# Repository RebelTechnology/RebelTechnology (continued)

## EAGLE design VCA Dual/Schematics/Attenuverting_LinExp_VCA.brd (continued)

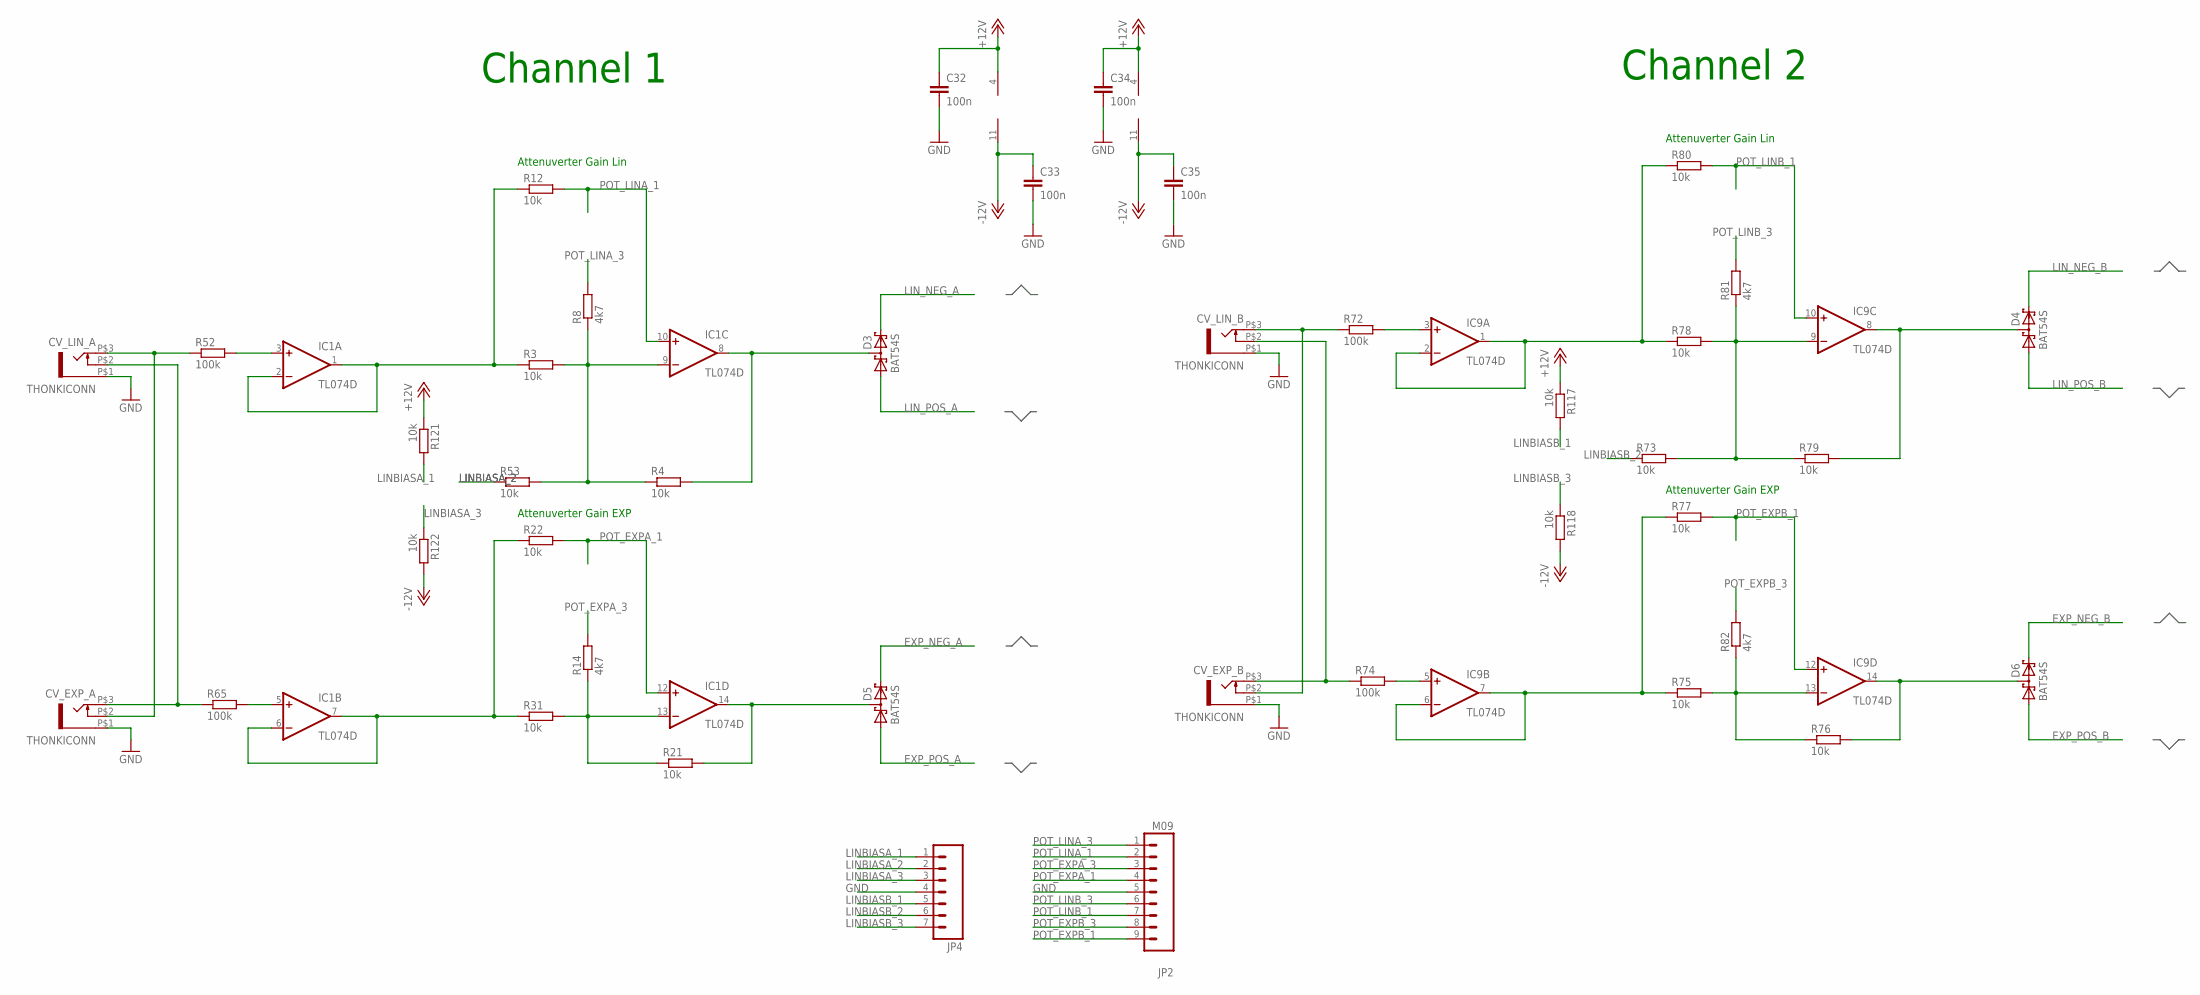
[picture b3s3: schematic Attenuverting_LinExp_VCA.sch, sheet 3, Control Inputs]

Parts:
C32, C33, C34, C35: 100n; C0603K
CV_EXP_A: THONKICONN
CV_EXP_B: THONKICONN
CV_LIN_A: THONKICONN
CV_LIN_B: THONKICONN
D3, D4, D5, D6: BAT54S; SOT23
IC1, IC9: TL074D; SO14
JP2: M09; 1X09
JP4: M07; 1X07
R3, R4, R12, R21, R22, R31, R53, R73, R75, R76, R77, R78, R79, R80, R117, R118, R121, R122: 10k; 0603
R8, R14, R81, R82: 4k7; 0603
R52, R65, R72, R74: 100k; 0603

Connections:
+12V: C32.1, C34.1, IC1.4 (V+), IC9.4 (V+), R117.1, R121.1; also elsewhere on the board
-12V: C33.1, C35.1, IC1.11 (V-), IC9.11 (V-), R118.2, R122.2; also elsewhere on the board
CV_1+: IC1.6 (-IN), IC1.7 (OUT), R22.1, R31.1
CV_1+1: IC9.6 (-IN), IC9.7 (OUT), R75.1, R77.1
CV_1-: IC1.1 (OUT), IC1.2 (-IN), R3.1, R12.1
CV_1-1: IC9.1 (OUT), IC9.2 (-IN), R78.1, R80.1
EXP_NEG_A: D5.2 (C2); also elsewhere on the board
EXP_NEG_B: D6.2 (C2); also elsewhere on the board
EXP_POS_A: D5.1 (A1); also elsewhere on the board
EXP_POS_B: D6.1 (A1); also elsewhere on the board
GND: C32.2, C33.2, C34.2, C35.2, CV_EXP_A.P$1 (5), CV_EXP_B.P$1 (5), CV_LIN_A.P$1 (5), CV_LIN_B.P$1 (5), JP2.5, JP4.4; also elsewhere on the board
LINBIASA_1: JP4.1, R121.2; also elsewhere on the board
LINBIASA_2: JP4.2, R53.1; also elsewhere on the board
LINBIASA_3: JP4.3, R122.1; also elsewhere on the board
LINBIASB_1: JP4.5, R117.2; also elsewhere on the board
LINBIASB_2: JP4.6, R73.1; also elsewhere on the board
LINBIASB_3: JP4.7, R118.1; also elsewhere on the board
LIN_NEG_A: D3.2 (C2); also elsewhere on the board
LIN_NEG_B: D4.2 (C2); also elsewhere on the board
LIN_POS_A: D3.1 (A1); also elsewhere on the board
LIN_POS_B: D4.1 (A1); also elsewhere on the board
unnamed: D3.3 (C1A2), IC1.8 (OUT), R4.2
unnamed: IC1.3 (+IN), R52.2
unnamed: IC1.5 (+IN), R65.2
unnamed: IC1.13 (-IN), R14.1, R21.1, R31.2
unnamed: IC1.9 (-IN), R3.2, R4.1, R8.1, R53.2
unnamed: CV_EXP_B.P$3 (3), CV_LIN_B.P$2 (4), R74.1
unnamed: CV_EXP_B.P$2 (4), CV_LIN_B.P$3 (3), R72.1
unnamed: D6.3 (C1A2), IC9.14 (OUT), R76.2
unnamed: IC9.13 (-IN), R75.2, R76.1, R82.1
unnamed: D4.3 (C1A2), IC9.8 (OUT), R79.2
unnamed: IC9.3 (+IN), R72.2
unnamed: IC9.5 (+IN), R74.2
unnamed: IC9.9 (-IN), R73.2, R78.2, R79.1, R81.1
unnamed: CV_EXP_A.P$3 (3), CV_LIN_A.P$2 (4), R65.1
unnamed: CV_EXP_A.P$2 (4), CV_LIN_A.P$3 (3), R52.1
unnamed: D5.3 (C1A2), IC1.14 (OUT), R21.2
POT_EXPA_1: IC1.12 (+IN), JP2.4, R22.2; also elsewhere on the board
POT_EXPA_3: JP2.3, R14.2; also elsewhere on the board
POT_EXPB_1: IC9.12 (+IN), JP2.9, R77.2; also elsewhere on the board
POT_EXPB_3: JP2.8, R82.2; also elsewhere on the board
POT_LINA_1: IC1.10 (+IN), JP2.2, R12.2; also elsewhere on the board
POT_LINA_3: JP2.1, R8.2; also elsewhere on the board
POT_LINB_1: IC9.10 (+IN), JP2.7, R80.2; also elsewhere on the board
POT_LINB_3: JP2.6, R81.2; also elsewhere on the board

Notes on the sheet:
Attenuverter Gain Lin
Attenuverter Gain EXP
Channel 1
Channel 2

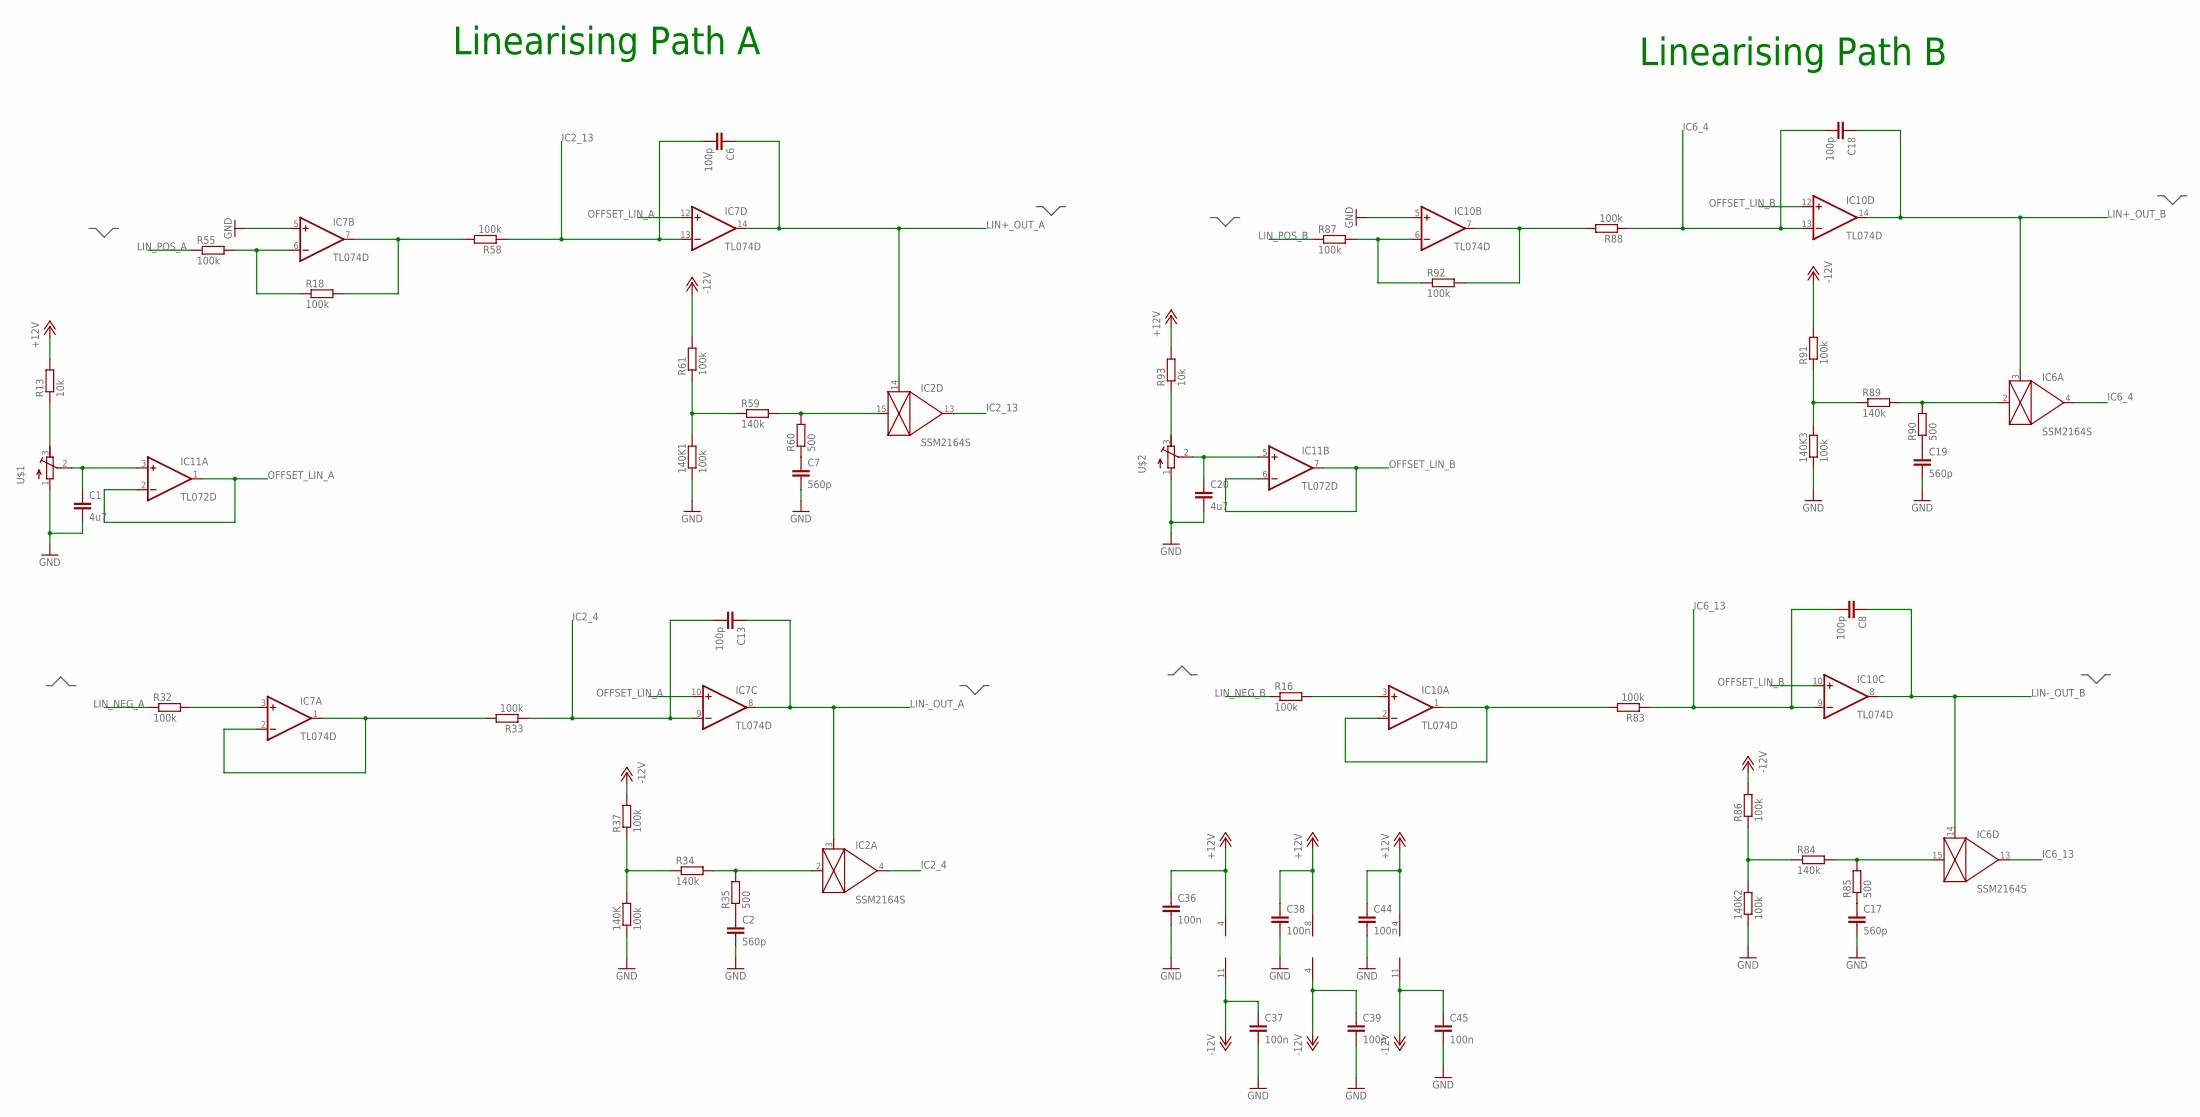
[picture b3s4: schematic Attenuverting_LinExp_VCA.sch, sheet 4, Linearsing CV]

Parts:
140K, 140K1, 140K2, 140K3: 100k; 0603
C1, C20: 4u7; C0603K
C2, C7, C17, C19: 560p; C0603K
C6, C8, C13, C18: 100p; C0603K
C36, C37, C38, C39, C44, C45: 100n; C0603K
IC2, IC6: SSM2164S; SOIC16N
IC7, IC10: TL074D; SO14
IC11: TL072D; SO08
R13, R93: 10k; 0603
R16, R18, R32, R33, R37, R55, R58, R61, R83, R86, R87, R88, R91, R92: 100k; 0603
R34, R59, R84, R89: 140k; 0603
R35, R60, R85, R90: 500; 0603
U$1, U$2: R-TRIMM64W; RTRIM64W

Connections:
+12V: C36.1, C38.1, C44.1, IC7.4 (V+), IC10.4 (V+), IC11.8 (V+), R13.2, R93.2; also elsewhere on the board
-10V: 140K.2, R34.1, R37.1
-10V1: 140K1.2, R59.1, R61.1
-10V2: 140K3.2, R89.1, R91.1
-10V3: 140K2.2, R84.1, R86.1
-12V: C37.1, C39.1, C45.1, IC7.11 (V-), IC10.11 (V-), IC11.4 (V-), R37.2, R61.2, R86.2, R91.2; also elsewhere on the board
GND: 140K.1, 140K1.1, 140K2.1, 140K3.1, C1.2, C2.2, C7.2, C17.2, C19.2, C20.2, C36.2, C37.2, C38.2, C39.2, C44.2, C45.2, IC7.5 (+IN), IC10.5 (+IN), U$1.1 (A), U$2.1 (A); also elsewhere on the board
IC2_4: C13.2, IC2.4 (OUT), IC7.9 (-IN), R33.1
IC2_13: C6.2, IC2.13 (OUT), IC7.13 (-IN), R58.1
IC6_4: C18.2, IC6.4 (OUT), IC10.13 (-IN), R88.1
IC6_13: C8.2, IC6.13 (OUT), IC10.9 (-IN), R83.1
LIN+_OUT_A: C6.1, IC2.14 (CTRL), IC7.14 (OUT); also elsewhere on the board
LIN+_OUT_B: C18.1, IC6.3 (CTRL), IC10.14 (OUT); also elsewhere on the board
LIN-_OUT_A: C13.1, IC2.3 (CTRL), IC7.8 (OUT); also elsewhere on the board
LIN-_OUT_B: C8.1, IC6.14 (CTRL), IC10.8 (OUT); also elsewhere on the board
LIN_NEG_A: R32.1; also elsewhere on the board
LIN_NEG_B: R16.1; also elsewhere on the board
LIN_POS_A: R55.1; also elsewhere on the board
LIN_POS_B: R87.1; also elsewhere on the board
unnamed: IC7.1 (OUT), IC7.2 (-IN), R33.2
unnamed: C2.1, R35.1
unnamed: IC2.2 (IN), R34.2, R35.2
unnamed: IC7.6 (-IN), R18.1, R55.2
unnamed: IC10.7 (OUT), R88.2, R92.2
unnamed: C19.1, R90.1
unnamed: R13.1, U$1.3 (E)
unnamed: C1.1, IC11.3 (+IN), U$1.2 (S)
unnamed: IC7.3 (+IN), R32.2
unnamed: IC7.7 (OUT), R18.2, R58.2
unnamed: C7.1, R60.1
unnamed: IC2.15 (IN), R59.2, R60.2
unnamed: IC6.2 (IN), R89.2, R90.2
unnamed: IC10.1 (OUT), IC10.2 (-IN), R83.2
unnamed: IC10.3 (+IN), R16.2
unnamed: C17.1, R85.1
unnamed: IC6.15 (IN), R84.2, R85.2
unnamed: IC10.6 (-IN), R87.2, R92.1
unnamed: R93.1, U$2.3 (E)
unnamed: C20.1, IC11.5 (+IN), U$2.2 (S)
OFFSET_LIN_A: IC7.10 (+IN), IC7.12 (+IN), IC11.1 (OUT), IC11.2 (-IN)
OFFSET_LIN_B: IC10.10 (+IN), IC10.12 (+IN), IC11.6 (-IN), IC11.7 (OUT)

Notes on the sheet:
Linearising Path A
Linearising Path B

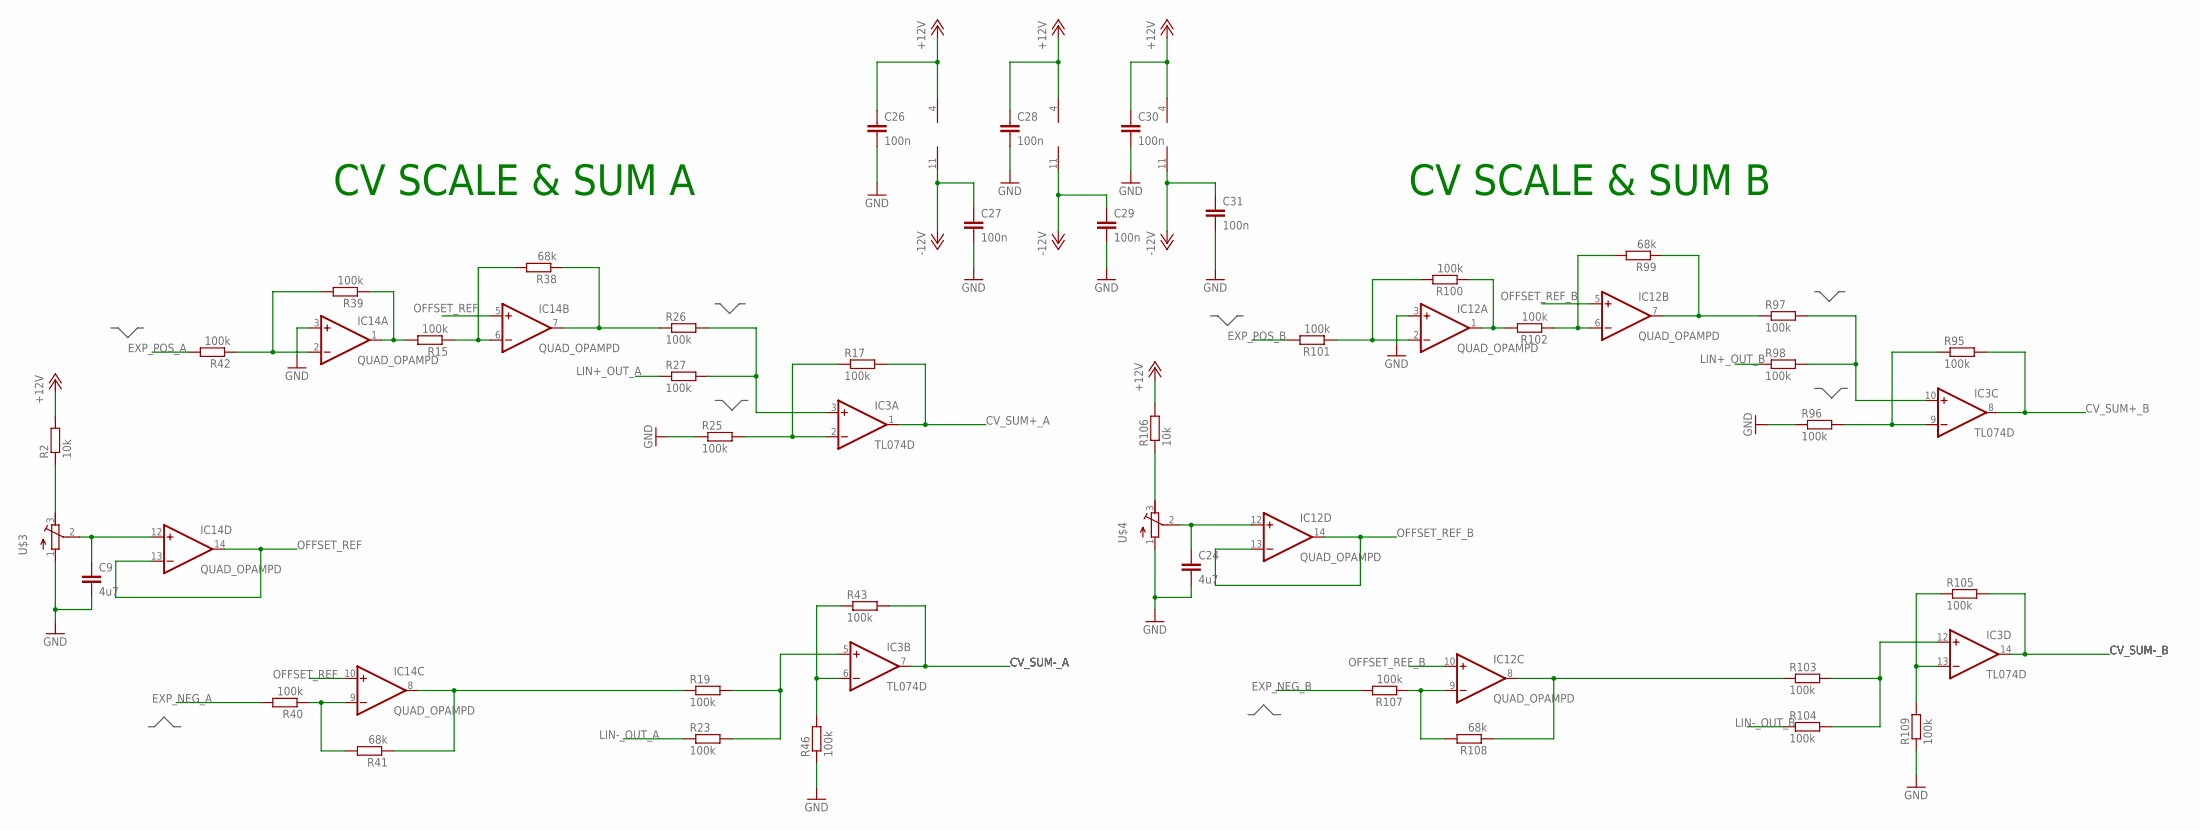
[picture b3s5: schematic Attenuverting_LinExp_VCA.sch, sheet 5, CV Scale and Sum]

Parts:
C9, C24: 4u7; C0603K
C26, C27, C28, C29, C30, C31: 100n; C0603K
IC3: TL074D; SO14
IC12, IC14: QUAD_OPAMPD; SO14
R2, R106: 10k; 0603
R15, R17, R19, R23, R25, R26, R27, R39, R40, R42, R43, R46, R95, R96, R97, R98, R100, R101, R102, R103, R104, R105, R107, R109: 100k; 0603
R38, R41, R99, R108: 68k; 0603
U$3, U$4: R-TRIMM64W; RTRIM64W

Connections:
+12V: C26.1, C28.1, C30.1, IC3.4 (V+), IC12.4 (V+), IC14.4 (V+), R2.2, R106.2; also elsewhere on the board
-12V: C27.1, C29.1, C31.1, IC3.11 (V-), IC12.11 (V-), IC14.11 (V-); also elsewhere on the board
CV_SUM+_A: IC3.1 (OUT), R17.2; also elsewhere on the board
CV_SUM+_B: IC3.8 (OUT), R95.2; also elsewhere on the board
CV_SUM-_A: IC3.7 (OUT), R43.2; also elsewhere on the board
CV_SUM-_B: IC3.14 (OUT), R105.2; also elsewhere on the board
EXP_NEG: IC14.8 (OUT), R19.1, R41.1
EXP_NEG1: IC12.8 (OUT), R103.1, R108.1
EXP_NEG_A: R40.2; also elsewhere on the board
EXP_NEG_B: R107.2; also elsewhere on the board
EXP_POS_A: R42.2; also elsewhere on the board
EXP_POS_B: R101.2; also elsewhere on the board
GND: C9.2, C24.2, C26.2, C27.2, C28.2, C29.2, C30.2, C31.2, IC12.3 (+IN), IC14.3 (+IN), R25.1, R46.1, R96.1, R109.1, U$3.1 (A), U$4.1 (A); also elsewhere on the board
IC2_1: IC12.7 (OUT), R97.1, R99.1
IC2_2: IC12.6 (-IN), R99.2, R102.1
IC2_7: IC14.7 (OUT), R26.1, R38.1
IC2_8: IC14.6 (-IN), R15.1, R38.2
LIN+_OUT_A: R27.1; also elsewhere on the board
LIN+_OUT_B: R98.1; also elsewhere on the board
LIN-_OUT_A: R23.1; also elsewhere on the board
LIN-_OUT_B: R104.1; also elsewhere on the board
unnamed: IC3.5 (+IN), R19.2, R23.2
unnamed: IC3.6 (-IN), R43.1, R46.2
unnamed: IC3.3 (+IN), R26.2, R27.2
unnamed: IC3.2 (-IN), R17.1, R25.2
unnamed: IC14.1 (OUT), R15.2, R39.1
unnamed: IC14.2 (-IN), R39.2, R42.1
unnamed: R2.1, U$3.3 (E)
unnamed: C9.1, IC14.12 (+IN), U$3.2 (S)
unnamed: IC14.9 (-IN), R40.1, R41.2
unnamed: IC3.10 (+IN), R97.2, R98.2
unnamed: IC3.9 (-IN), R95.1, R96.2
unnamed: IC12.2 (-IN), R100.2, R101.1
unnamed: IC12.1 (OUT), R100.1, R102.2
unnamed: IC3.12 (+IN), R103.2, R104.2
unnamed: R106.1, U$4.3 (E)
unnamed: C24.1, IC12.12 (+IN), U$4.2 (S)
unnamed: IC12.9 (-IN), R107.1, R108.2
unnamed: IC3.13 (-IN), R105.1, R109.2
OFFSET_REF: IC14.5 (+IN), IC14.10 (+IN), IC14.13 (-IN), IC14.14 (OUT)
OFFSET_REF_B: IC12.5 (+IN), IC12.10 (+IN), IC12.13 (-IN), IC12.14 (OUT)

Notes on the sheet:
CV SCALE & SUM A
CV SCALE & SUM B

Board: 2 copper layers, 234 parts (0 on the bottom side), 162 nets, no tracks yet.

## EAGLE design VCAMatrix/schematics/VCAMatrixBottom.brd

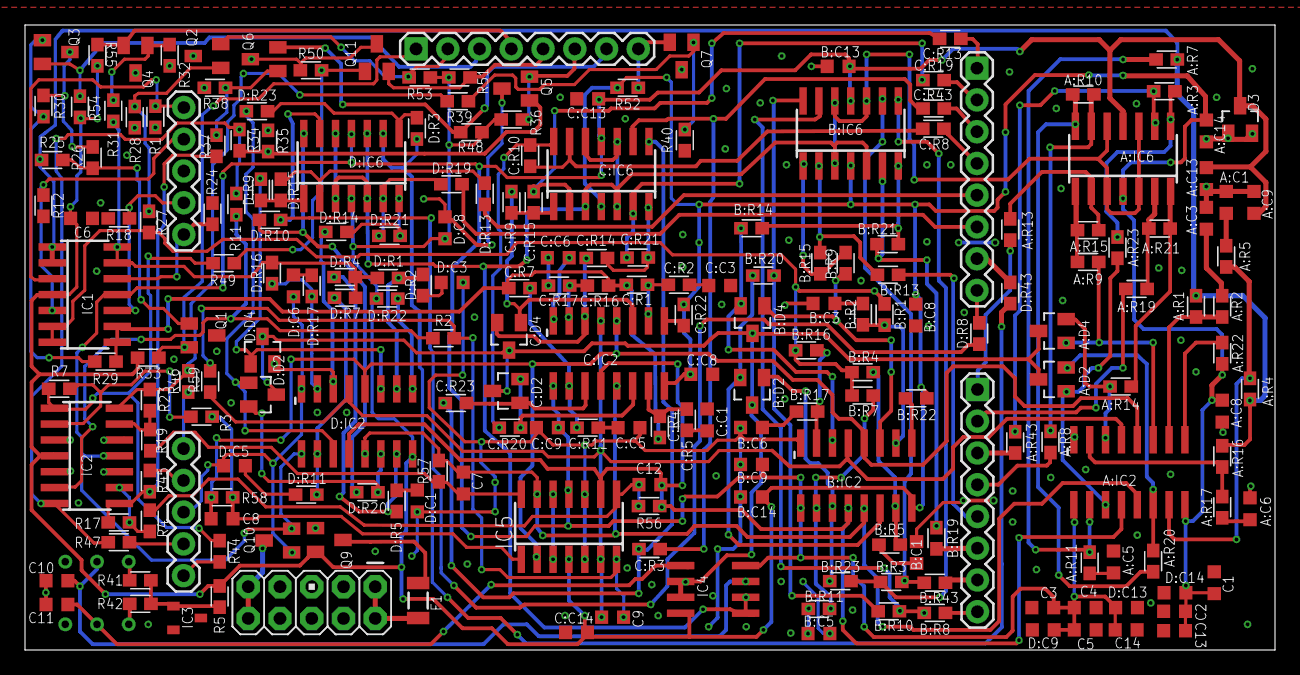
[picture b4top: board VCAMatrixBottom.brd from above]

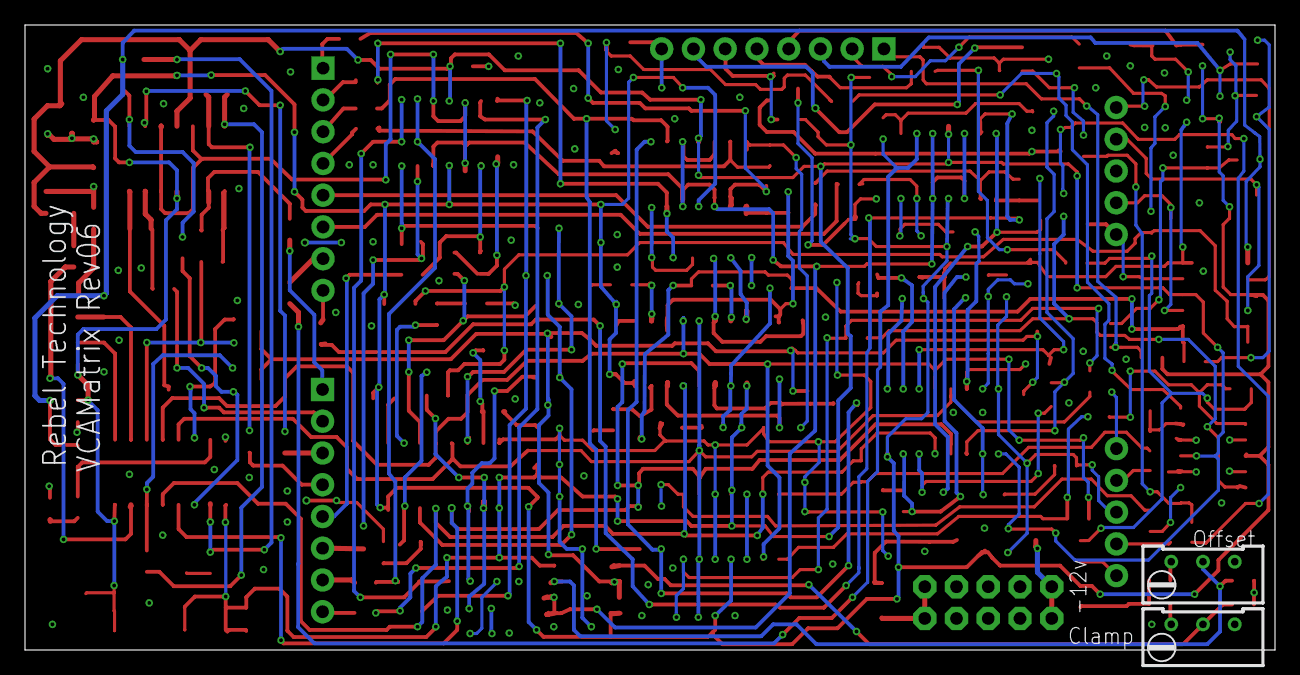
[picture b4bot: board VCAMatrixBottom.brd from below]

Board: 2 copper layers, 100.0 x 50.0 mm, 218 parts (2 on the bottom side), 157 nets.

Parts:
A:C1, A:C3, A:C5, A:C6: 560p; C0603K
A:C8, A:C9, A:C13, A:C14: 100n; C0603K
A:D2, A:D4: BAT54A; SOT23
A:IC2: SSM2164S; SOIC16N
A:IC6: QUAD_OPAMPD; SO14
A:R1, A:R4, A:R7, A:R16: 30k; 0603
A:R2, A:R5, A:R9, A:R11, A:R14, A:R17, A:R20, A:R23: 510R; 0603
A:R3, A:R10, A:R15, A:R21: 68k; 0603
A:R8, A:R13, A:R19, A:R43: 100k; 0603
A:R22: 5k1; 0603
B:C1, B:C3, B:C5, B:C6: 560p; C0603K
B:C8, B:C9, B:C13, B:C14: 100n; C0603K
B:D2, B:D4: BAT54A; SOT23
B:IC2: SSM2164S; SOIC16N
B:IC6: QUAD_OPAMPD; SO14
B:R1, B:R4, B:R7, B:R16: 30k; 0603
B:R2, B:R5, B:R9, B:R11, B:R14, B:R17, B:R20, B:R23: 510R; 0603
B:R3, B:R10, B:R15, B:R21: 68k; 0603
B:R8, B:R13, B:R19, B:R43: 100k; 0603
B:R22: 5k1; 0603
C1, C2, C3, C4, C5, C6, C13, C14: 100n; C0603K
C7, C8, C9, C12: 100p; C0603K
C10, C11: 4u7; C0603K
C:C1, C:C3, C:C5, C:C6: 560p; C0603K
C:C8, C:C9, C:C13, C:C14: 100n; C0603K
C:D2, C:D4: BAT54A; SOT23
C:IC2: SSM2164S; SOIC16N
C:IC6: QUAD_OPAMPD; SO14
C:R1, C:R4, C:R7, C:R16: 30k; 0603
C:R2, C:R5, C:R9, C:R11, C:R14, C:R17, C:R20, C:R23: 510R; 0603
C:R3, C:R10, C:R15, C:R21: 68k; 0603
C:R8, C:R13, C:R19, C:R43: 100k; 0603
C:R22: 5k1; 0603
CLAMP: 10k lin; RTRIM64W
D3: BAT54A; SOT23
D:C1, D:C3, D:C5, D:C6: 560p; C0603K
D:C8, D:C9, D:C13, D:C14: 100n; C0603K
D:D2, D:D4: BAT54A; SOT23
D:IC2: SSM2164S; SOIC16N
D:IC6: QUAD_OPAMPD; SO14
D:R1, D:R4, D:R7, D:R16: 30k; 0603
D:R2, D:R5, D:R9, D:R11, D:R14, D:R17, D:R20, D:R23: 510R; 0603
D:R3, D:R10, D:R15, D:R21: 68k; 0603
D:R8, D:R13, D:R19, D:R43: 100k; 0603
D:R22: 5k1; 0603
F1: PTCSMD; PTC-1206
IC1, IC2, IC5: QUAD_OPAMPD; SO14
IC3: LM4040B10; DBZ_R-PDSO-G3
IC4: TL072D; SO08
J3, J4: 1X05
JP1, JP3, JP5: 1X08
JP8: M05X2PTH; AVR_ICSP
OFFSET: 10k lin; RTRIM64W
Q1, Q2, Q3, Q4, Q5, Q6, Q7, Q11: BC856ALT1SMD; SOT23-BEC
Q9: BSS84; SOT23
Q10: BSS123; SOT23
R1, R12, R18, R24, R25, R26, R27, R28, R29, R30, R31, R32, R34, R35, R37, R38, R39, R40, R42, R49, R50: 100k; 0603
R2, R3, R4, R7, R11, R17, R19, R23, R41: 10k; 0603
R5: 510R; 0603
R33, R36, R48, R51, R52, R53, R54, R55: 2k7; 0603
R44, R45, R46, R47: 1k; 0603
R56, R57, R58, R59: 30k; 0603

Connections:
+12V: A:C8.1, A:C14.1, A:IC2.16, A:IC6.4, A:R22.2, B:C8.1, B:C14.1, B:IC2.16, B:IC6.4, B:R22.2, C1.1, C2.1, C6.1, C13.1, C:C8.1, C:C14.1, C:IC2.16, C:IC6.4, C:R22.2, D:C8.1, D:C14.1, D:IC2.16, D:IC6.4, D:R22.2, IC1.4, IC2.4, IC4.8, IC5.4, Q9.2, R5.2, R33.2, R36.2, R48.2, R51.2, R52.2, R53.2, R54.2, R55.2
-12V: A:C9.2, A:C13.1, A:IC2.9, A:IC6.11, B:C9.2, B:C13.1, B:IC2.9, B:IC6.11, C3.1, C4.1, C5.1, C14.1, C:C9.2, C:C13.1, C:IC2.9, C:IC6.11, D3.3, D:C9.2, D:C13.1, D:IC2.9, D:IC6.11, IC1.11, IC2.11, IC4.4, IC5.11, Q10.2
A:IC2_1: A:IC6.14, A:R10.1, A:R20.1
A:IC2_2: A:IC6.13, A:R8.1, A:R10.2
A:IC2_3: A:IC6.1, A:R9.1, A:R15.1
A:IC2_4: A:IC6.9, A:R3.2, A:R43.1
A:IC2_5: A:IC6.2, A:R13.1, A:R15.2
A:IC2_6: A:IC6.7, A:R14.1, A:R21.1
A:IC2_7: A:IC6.6, A:R19.1, A:R21.2
A:IC2_11: A:IC6.8, A:R3.1, A:R23.2
A:N$1: A:D4.1, A:IC2.3, A:R9.2
A:N$2: A:C1.1, A:R5.1
A:N$3: A:C3.1, A:R2.1
A:N$4: A:IC2.15, A:R4.2, A:R5.2
A:N$5: A:IC2.2, A:R1.2, A:R2.2
A:N$7: A:D4.2, A:IC2.6, A:R14.2
A:N$8: A:D2.1, A:IC2.11, A:R23.1
A:N$11: A:C6.1, A:R17.1
A:N$12: A:IC2.7, A:R16.2, A:R17.2
A:N$14: A:D2.2, A:IC2.14, A:R20.2
A:N$17: A:IC2.1, A:R22.1
A:N$19: A:C5.1, A:R11.1
A:N$23: A:IC2.10, A:R7.2, A:R11.2
B:IC2_1: B:IC6.14, B:R10.1, B:R20.1
B:IC2_2: B:IC6.13, B:R8.1, B:R10.2
B:IC2_3: B:IC6.1, B:R9.1, B:R15.1
B:IC2_4: B:IC6.9, B:R3.2, B:R43.1
B:IC2_5: B:IC6.2, B:R13.1, B:R15.2
B:IC2_6: B:IC6.7, B:R14.1, B:R21.1
B:IC2_7: B:IC6.6, B:R19.1, B:R21.2
B:IC2_11: B:IC6.8, B:R3.1, B:R23.2
B:N$1: B:D4.1, B:IC2.3, B:R9.2
B:N$2: B:C1.1, B:R5.1
B:N$3: B:C3.1, B:R2.1
B:N$4: B:IC2.15, B:R4.2, B:R5.2
B:N$5: B:IC2.2, B:R1.2, B:R2.2
B:N$7: B:D4.2, B:IC2.6, B:R14.2
B:N$8: B:D2.1, B:IC2.11, B:R23.1
B:N$11: B:C6.1, B:R17.1
B:N$12: B:IC2.7, B:R16.2, B:R17.2
B:N$14: B:D2.2, B:IC2.14, B:R20.2
B:N$17: B:IC2.1, B:R22.1
B:N$19: B:C5.1, B:R11.1
B:N$23: B:IC2.10, B:R7.2, B:R11.2
C:IC2_1: C:IC6.14, C:R10.1, C:R20.1
C:IC2_2: C:IC6.13, C:R8.1, C:R10.2
C:IC2_3: C:IC6.1, C:R9.1, C:R15.1
C:IC2_4: C:IC6.9, C:R3.2, C:R43.1
C:IC2_5: C:IC6.2, C:R13.1, C:R15.2
C:IC2_6: C:IC6.7, C:R14.1, C:R21.1
C:IC2_7: C:IC6.6, C:R19.1, C:R21.2
C:IC2_11: C:IC6.8, C:R3.1, C:R23.2
C:N$1: C:D4.1, C:IC2.3, C:R9.2
C:N$2: C:C1.1, C:R5.1
C:N$3: C:C3.1, C:R2.1
C:N$4: C:IC2.15, C:R4.2, C:R5.2
C:N$5: C:IC2.2, C:R1.2, C:R2.2
C:N$7: C:D4.2, C:IC2.6, C:R14.2
C:N$8: C:D2.1, C:IC2.11, C:R23.1
C:N$11: C:C6.1, C:R17.1
C:N$12: C:IC2.7, C:R16.2, C:R17.2
C:N$14: C:D2.2, C:IC2.14, C:R20.2
C:N$17: C:IC2.1, C:R22.1
C:N$19: C:C5.1, C:R11.1
C:N$23: C:IC2.10, C:R7.2, C:R11.2
CLAMP_REF: A:D2.3, A:D4.3, B:D2.3, B:D4.3, C:D2.3, C:D4.3, D:D2.3, D:D4.3, IC4.6, IC4.7
CV_AA: A:R13.2, JP1.1
CV_AB: A:R19.2, JP1.2
CV_AC: A:R43.2, JP1.3
CV_AD: A:R8.2, JP1.4
CV_BA: B:R13.2, JP1.5
CV_BB: B:R19.2, JP1.6
CV_BC: B:R43.2, JP1.7
CV_BD: B:R8.2, JP1.8
CV_CA: C:R13.2, JP3.1
CV_CB: C:R19.2, JP3.2
CV_CC: C:R43.2, JP3.3
CV_CD: C:R8.2, JP3.4
CV_DA: D:R13.2, JP3.5
CV_DB: D:R19.2, JP3.6
CV_DC: D:R43.2, JP3.7
CV_DD: D:R8.2, JP3.8
CV_REF: IC3.1, R5.1, R41.2, R42.2
D:IC2_1: D:IC6.14, D:R10.1, D:R20.1
D:IC2_2: D:IC6.13, D:R8.1, D:R10.2
D:IC2_3: D:IC6.1, D:R9.1, D:R15.1
D:IC2_4: D:IC6.9, D:R3.2, D:R43.1
D:IC2_5: D:IC6.2, D:R13.1, D:R15.2
D:IC2_6: D:IC6.7, D:R14.1, D:R21.1
D:IC2_7: D:IC6.6, D:R19.1, D:R21.2
D:IC2_11: D:IC6.8, D:R3.1, D:R23.2
D:N$1: D:D4.1, D:IC2.3, D:R9.2
D:N$2: D:C1.1, D:R5.1
D:N$3: D:C3.1, D:R2.1
D:N$4: D:IC2.15, D:R4.2, D:R5.2
D:N$5: D:IC2.2, D:R1.2, D:R2.2
D:N$7: D:D4.2, D:IC2.6, D:R14.2
D:N$8: D:D2.1, D:IC2.11, D:R23.1
D:N$11: D:C6.1, D:R17.1
D:N$12: D:IC2.7, D:R16.2, D:R17.2
D:N$14: D:D2.2, D:IC2.14, D:R20.2
D:N$17: D:IC2.1, D:R22.1
D:N$19: D:C5.1, D:R11.1
D:N$23: D:IC2.10, D:R7.2, D:R11.2
GND: A:C1.2, A:C3.2, A:C5.2, A:C6.2, A:C8.2, A:C9.1, A:C13.2, A:C14.2, A:IC2.8, B:C1.2, B:C3.2, B:C5.2, B:C6.2, B:C8.2, B:C9.1, B:C13.2, B:C14.2, B:IC2.8, C1.2, C2.2, C3.2, C4.2, C5.2, C6.2, C10.2, C11.2, C13.2, C14.2, C:C1.2, C:C3.2, C:C5.2, C:C6.2, C:C8.2, C:C9.1, C:C13.2, C:C14.2, C:IC2.8, CLAMP.1, D3.1, D3.2, D:C1.2, D:C3.2, D:C5.2, D:C6.2, D:C8.2, D:C9.1, D:C13.2, D:C14.2, D:IC2.8, IC2.3, IC2.5, IC2.10, IC2.12, IC3.2, IC5.3, IC5.5, IC5.10, IC5.12, J3.3, J4.3, JP8.3, JP8.4, JP8.5, JP8.6, JP8.7, JP8.8, OFFSET.1, Q1.C, Q2.C, Q3.C, Q4.C, Q5.C, Q6.C, Q7.C, Q9.1, Q10.1, Q11.C, R1.1, R12.1, R18.1, R24.1, R26.1, R28.1, R30.1, R32.1, R35.1, R38.1, R40.1, R50.1
IN_A: IC1.3, J3.5, R1.2
IN_B: IC1.5, J3.4, R12.2
IN_C: IC1.10, J3.2, R18.2
IN_D: IC1.12, J3.1, R24.2
ITOV_A: C8.1, IC5.1, R3.1, R58.2
ITOV_B: C9.1, IC5.7, R2.1, R59.2
ITOV_C: C12.1, IC5.8, R4.1, R56.2
ITOV_D: C7.1, IC5.14, R19.1, R57.2
LED_1: JP5.1, Q1.E, R33.1
LED_2: JP5.2, Q2.E, R53.1
LED_3: JP5.3, Q3.E, R54.1
LED_4: JP5.4, Q4.E, R55.1
LED_5: JP5.5, Q11.E, R51.1
LED_6: JP5.6, Q5.E, R36.1
LED_7: JP5.7, Q6.E, R48.1
LED_8: JP5.8, Q7.E, R52.1
unnamed: B:R1.1, B:R4.1, B:R7.1, B:R16.1, IC1.6, IC1.7, R27.1
unnamed: Q1.B, R25.2, R26.2
unnamed: JP8.9, JP8.10, Q10.3
unnamed: Q2.B, R27.2, R28.2
unnamed: IC2.2, R3.2, R7.1
unnamed: A:IC2.4, B:IC2.4, C8.2, C:IC2.4, D:IC2.4, IC5.2, R58.1
unnamed: A:IC2.12, B:IC2.12, C12.2, C:IC2.12, D:IC2.12, IC5.9, R56.1
unnamed: A:IC2.5, B:IC2.5, C9.2, C:IC2.5, D:IC2.5, IC5.6, R59.1
unnamed: IC2.9, R4.2, R17.1
unnamed: Q11.B, R49.2, R50.2
unnamed: OFFSET.3, R41.1
unnamed: Q5.B, R34.2, R35.2
unnamed: Q6.B, R37.2, R38.2
unnamed: Q7.B, R39.2, R40.2
unnamed: F1.2, Q9.3
unnamed: A:IC2.13, B:IC2.13, C7.2, C:IC2.13, D:IC2.13, IC5.13, R57.1
unnamed: Q3.B, R29.2, R30.2
unnamed: D:R1.1, D:R4.1, D:R7.1, D:R16.1, IC1.13, IC1.14, R31.1
unnamed: C:R1.1, C:R4.1, C:R7.1, C:R16.1, IC1.8, IC1.9, R29.1
unnamed: Q4.B, R31.2, R32.2
unnamed: C10.1, IC4.3, OFFSET.2
unnamed: CLAMP.3, R42.1
unnamed: IC2.13, R19.2, R23.1
unnamed: IC2.6, R2.2, R11.1
unnamed: C11.1, CLAMP.2, IC4.5
unnamed: F1.1, JP8.1, JP8.2
unnamed: A:R1.1, A:R4.1, A:R7.1, A:R16.1, IC1.1, IC1.2, R25.1
OFFSET_REF: A:IC6.3, A:IC6.5, A:IC6.10, A:IC6.12, B:IC6.3, B:IC6.5, B:IC6.10, B:IC6.12, C:IC6.3, C:IC6.5, C:IC6.10, C:IC6.12, D:IC6.3, D:IC6.5, D:IC6.10, D:IC6.12, IC4.1, IC4.2
OUTPUT_A: J4.5, R44.1
OUTPUT_B: J4.4, R47.1
OUTPUT_C: J4.2, R45.1
OUTPUT_D: J4.1, R46.1
OUT_A: IC2.1, R7.2, R44.2, R49.1
OUT_B: IC2.7, R11.2, R34.1, R47.2
OUT_C: IC2.8, R17.2, R37.1, R45.2
OUT_D: IC2.14, R23.2, R39.1, R46.2
